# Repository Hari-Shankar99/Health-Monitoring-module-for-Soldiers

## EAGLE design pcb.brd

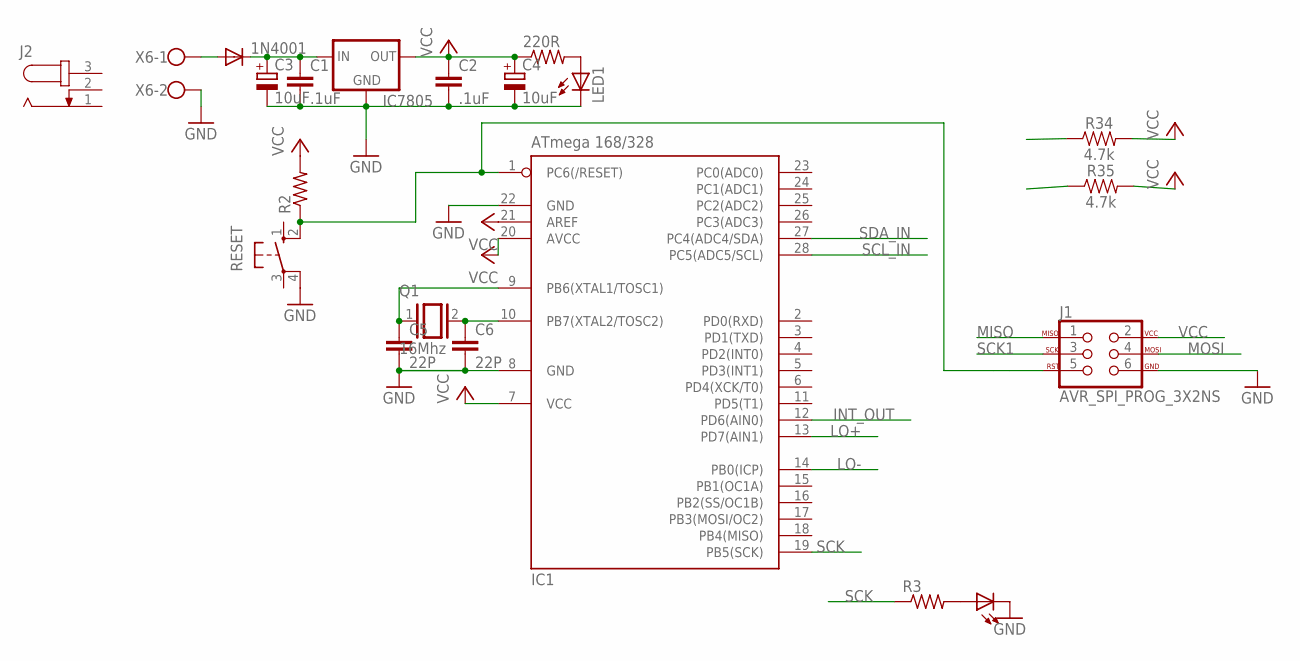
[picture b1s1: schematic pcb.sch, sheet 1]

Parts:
1N4001: BYT85; DO220S
220R: R-US_0204/7; 0204/7
C1, C2: .1uF; C025-024X044
C3, C4: 10uF; E1,8-4
C5, C6: 22P; C025-024X044
IC1: ATmega 168/328; DIL28-3
IC7805: 78XXS
J1: AVR_SPI_PROG_3X2NS; 2X3-NS
J2: JACK-PLUG0; SPC4077
LED1, LED2: LED3MM
Q1: 16Mhz; QS
R2, R3: R-US_0204/7; 0204/7
R34, R35: 4.7k; 0603
RESET: 10-XX; B3F-10XX
X6: W237-102

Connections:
GND: C1.2, C2.2, C3.-, C4.-, C5.2, C6.2, IC1.8 (GND), IC1.22 (GND), IC7805.GND, J1.6, LED1.K (C), LED2.K (C), RESET.4 (P1), X6.2; also elsewhere on the board
INT_OUT: IC1.12 (PD6(AIN0)); also elsewhere on the board
LO+: IC1.13 (PD7(AIN1)); also elsewhere on the board
LO-: IC1.14 (PB0(ICP)); also elsewhere on the board
MISO: J1.1
MOSI: J1.4
unnamed: 1N4001.C, C1.1, C3.+, IC7805.IN
unnamed: 1N4001.A, X6.1
unnamed: 220R.2, LED1.A
unnamed: C6.1, IC1.10 (PB7(XTAL2/TOSC2)), Q1.2
unnamed: C5.1, IC1.9 (PB6(XTAL1/TOSC1)), Q1.1
unnamed: IC1.1 (PC6(/RESET)), J1.5, R2.1, RESET.2 (S1)
unnamed: LED2.A, R3.2
SCK: IC1.19 (PB5(SCK)), R3.1
SCK1: J1.3
SCL_IN: IC1.28 (PC5(ADC5/SCL)); also elsewhere on the board
SDA_IN: IC1.27 (PC4(ADC4/SDA)); also elsewhere on the board
VCC: 220R.1, C2.1, C4.+, IC1.7 (VCC), IC1.20 (AVCC), IC1.21 (AREF), IC7805.OUT, J1.2, R2.2, R34.2, R35.2; also elsewhere on the board

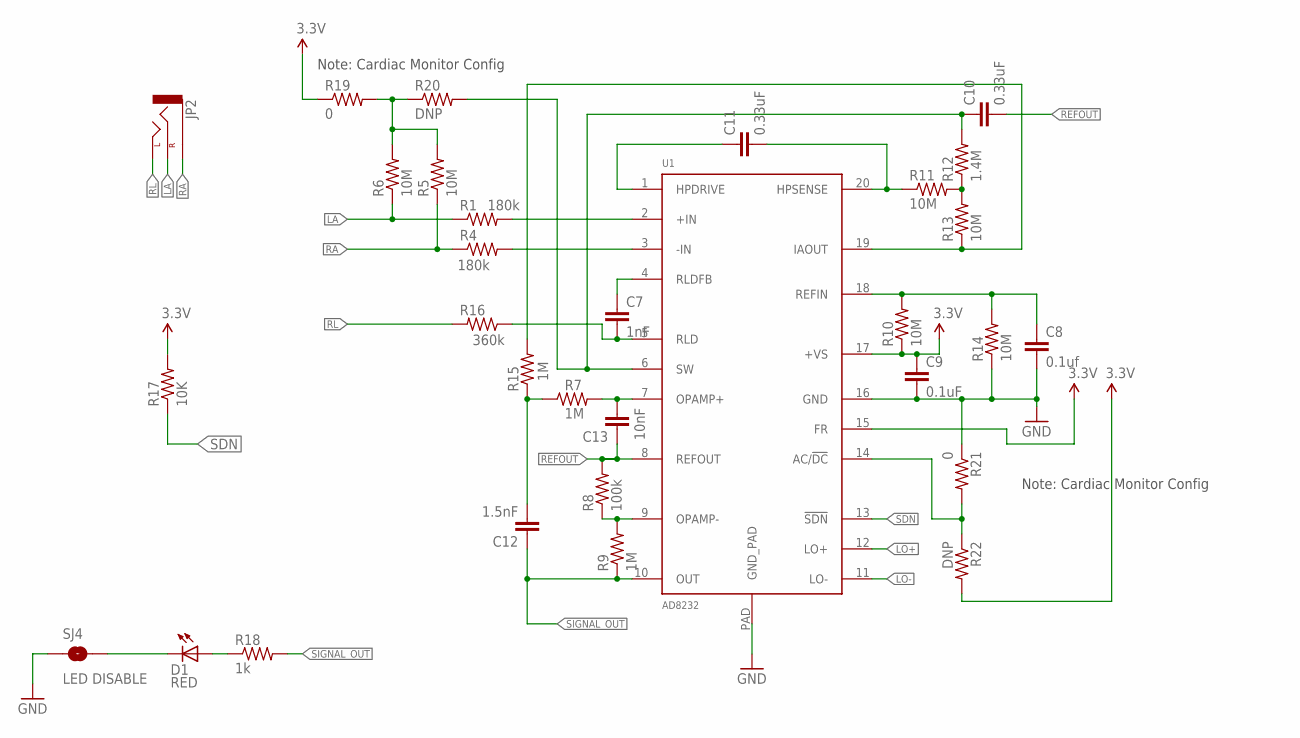
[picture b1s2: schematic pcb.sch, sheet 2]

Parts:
C7: 1nF; 0603-CAP
C8: 0.1uf; 0603-CAP
C9: 0.1uF; 0603-CAP
C10, C11: 0.33uF; 0805
C12: 1.5nF; 0603-CAP
C13: 10nF; 0603-CAP
D1: RED; LED-0603
JP2: AUDIO-JACKSMD2; AUDIO-JACK-3.5MM-SMD
R1, R4: 180k; 0603-RES
R5, R6, R10, R11, R13, R14: 10M; 0603-RES
R7, R9, R15: 1M; 0603-RES
R8: 100k; 0603-RES
R12: 1.4M; 0603-RES
R16: 360k; 0603-RES
R17: 10K; 0603-RES
R18: 1k; 0603-RES
R19, R21: 0; 0603
R20, R22: DNP; 0603
SJ4: LED DISABLE; SJ_2S-TRACE
U1: AD8232; LFCSP_20

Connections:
3.3V: C9.1, R10.1, R17.2, R19.1, R22.2, U1.15 (FR), U1.17 (+VS)
GND: C8.2, C9.2, R14.1, R21.1, SJ4.1, U1.16 (GND), U1.PAD (GND_PAD); also elsewhere on the board
LA: JP2.RING (RIGHT), R1.1, R6.1
LO+: U1.12 (LO+); also elsewhere on the board
LO-: U1.11 (LO-); also elsewhere on the board
unnamed: R1.2, U1.2 (+IN)
unnamed: R4.2, U1.3 (-IN)
unnamed: C13.2, R7.2, U1.7 (OPAMP+)
unnamed: C11.2, R11.1, U1.20 (HPSENSE)
unnamed: C8.1, R10.2, R14.2, U1.18 (REFIN)
unnamed: R8.1, R9.2, U1.9 (OPAMP-)
unnamed: C11.1, U1.1 (HPDRIVE)
unnamed: R11.2, R12.1, R13.2
unnamed: C10.1, R12.2, R20.2, U1.6 (SW)
unnamed: C7.1, U1.4 (RLDFB)
unnamed: C12.2, R7.1, R15.1
unnamed: C7.2, R16.1, U1.5 (RLD)
unnamed: R13.1, R15.2, U1.19 (IAOUT)
unnamed: R5.2, R6.2, R19.2, R20.1
unnamed: D1.A, R18.1
unnamed: D1.C, SJ4.2
unnamed: R21.2, R22.1, U1.14 (AC/!DC)
RA: JP2.SLEEVE, R4.1, R5.1
REFOUT: C10.2, C13.1, R8.2, U1.8 (REFOUT)
RL: JP2.TIP (LEFT), R16.2
SDN: R17.1, U1.13 (!SDN)
SIGNAL_OUT: C12.1, R9.1, R18.2, U1.10 (OUT)

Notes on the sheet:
Note: Cardiac Monitor Config

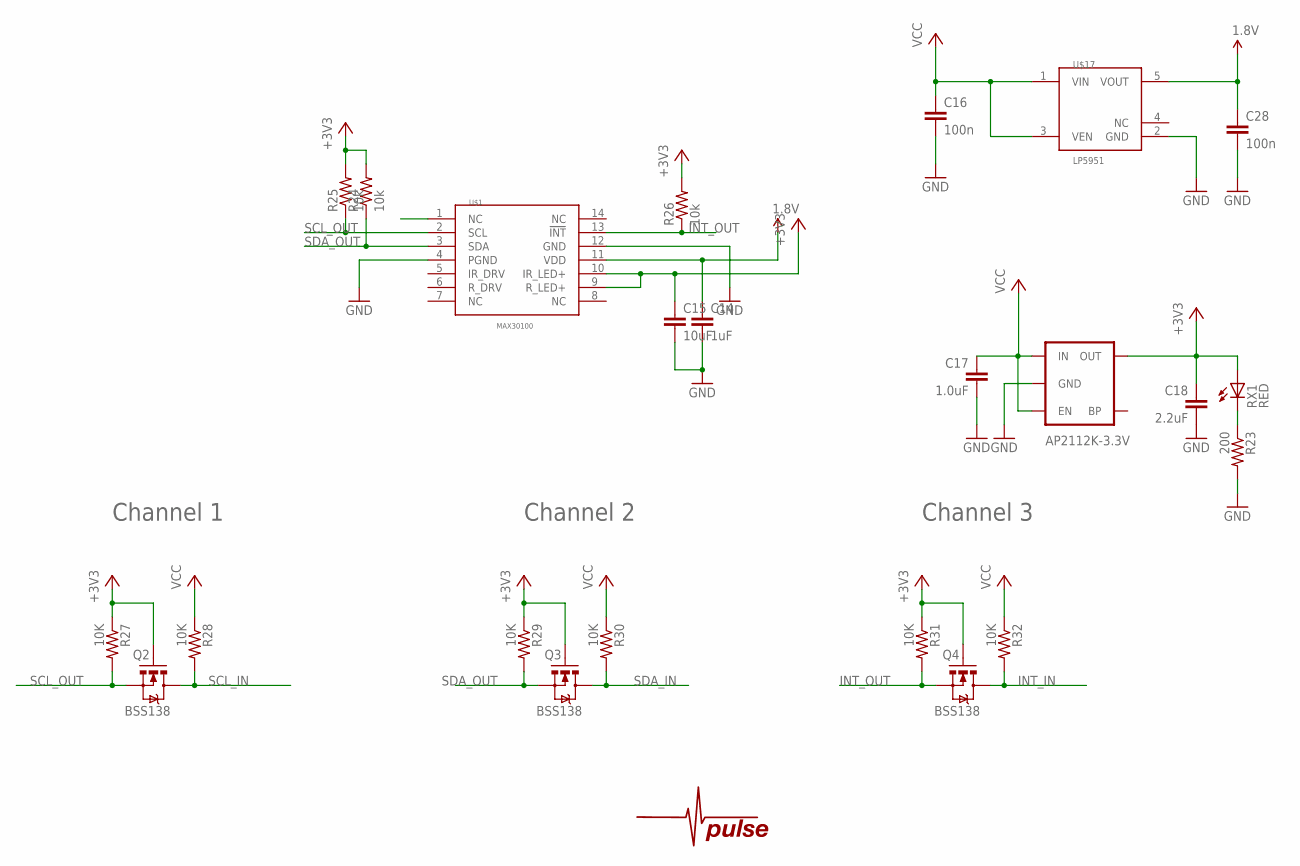
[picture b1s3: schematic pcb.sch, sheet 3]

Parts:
C14: 1uF; C0805
C15: 10uF; C0805
C16, C28: 100n; C0402
C17: 1.0uF; 0805
C18: 2.2uF; C0805
Q2, Q3, Q4: BSS138; SOT23-3
R23: 200; R0402
R24, R25, R26: 10k; R0402
R27, R28, R29, R30, R31, R32: 10K; 0402-RES
RX1: RED; CHIPLED_0603
U2: AP2112K-3.3V; SOT23-5
U$1: MAX30100; OESIP-14
U$3: PROTY_LOGO_WITH_TEXT; PROTY_WITH_TEXT
U$4: PULSE
U$17: LP5951; SC70-5

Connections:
1.8V: C14.1, C28.1, U$1.11 (VDD), U$17.5 (VOUT)
+3V3: C15.1, C18.1, Q2.1 (G), Q3.1 (G), Q4.1 (G), R24.2, R25.2, R26.2, R27.1, R29.1, R31.1, RX1.A, U2.5 (OUT), U$1.9 (R_LED+), U$1.10 (IR_LED+)
GND: C14.2, C15.2, C16.2, C17.2, C18.2, C28.2, R23.2, U2.2 (GND), U$1.4 (PGND), U$1.12 (GND), U$17.2 (GND); also elsewhere on the board
INT_IN: Q4.3 (D), R32.2
INT_OUT: Q4.2 (S), R26.1, R31.2, U$1.13 (!INT); also elsewhere on the board
unnamed: R23.1, RX1.C
unnamed: C17.1, U2.1 (IN), U2.3 (EN)
SCL_IN: Q2.3 (D), R28.2; also elsewhere on the board
SCL_OUT: Q2.2 (S), R25.1, R27.2, U$1.2 (SCL)
SDA_IN: Q3.3 (D), R30.2; also elsewhere on the board
SDA_OUT: Q3.2 (S), R24.1, R29.2, U$1.3 (SDA)
VCC: C16.1, R28.1, R30.1, R32.1, U$17.1 (VIN), U$17.3 (VEN); also elsewhere on the board

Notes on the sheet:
Channel 1
Channel 2
Channel 3

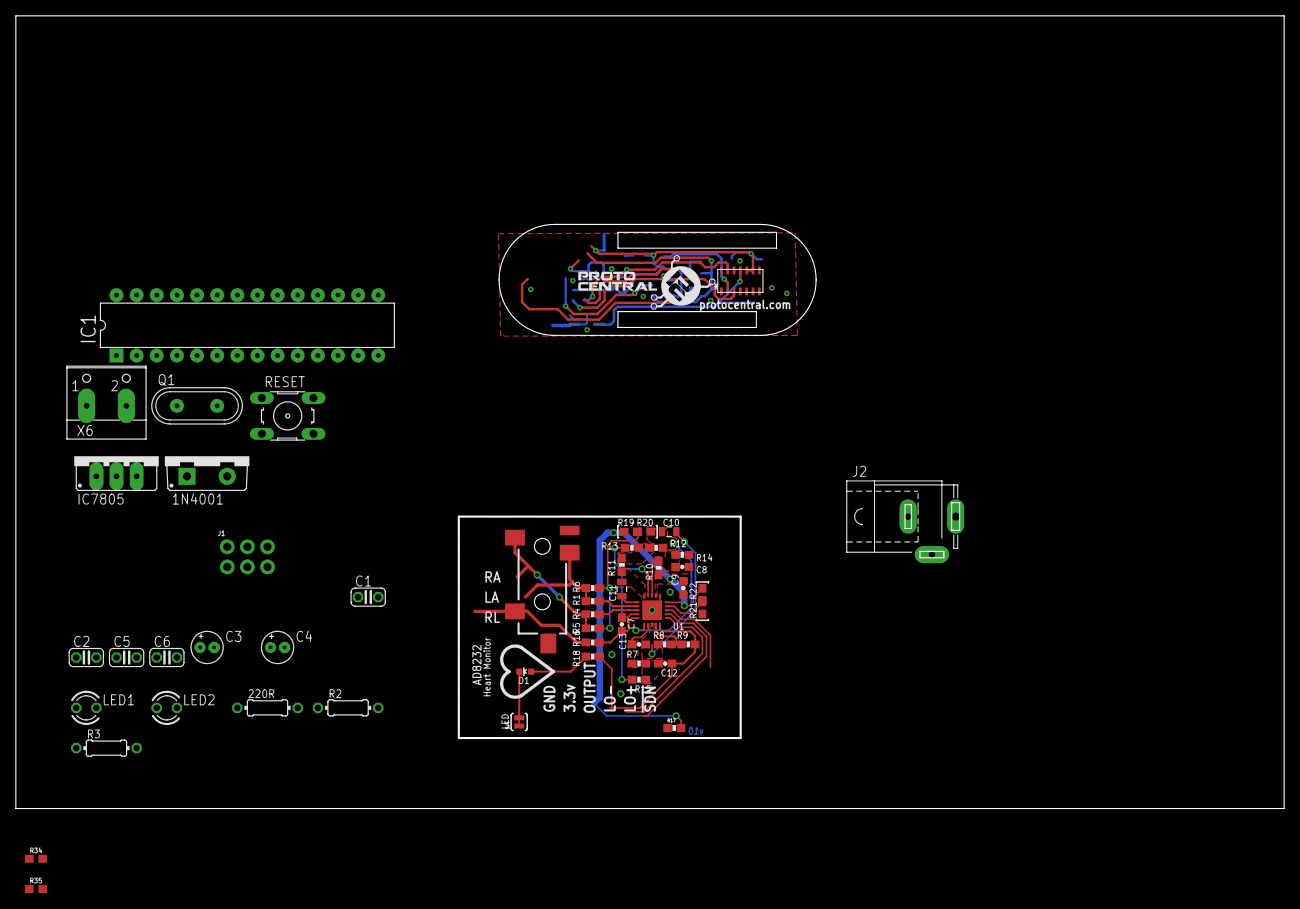
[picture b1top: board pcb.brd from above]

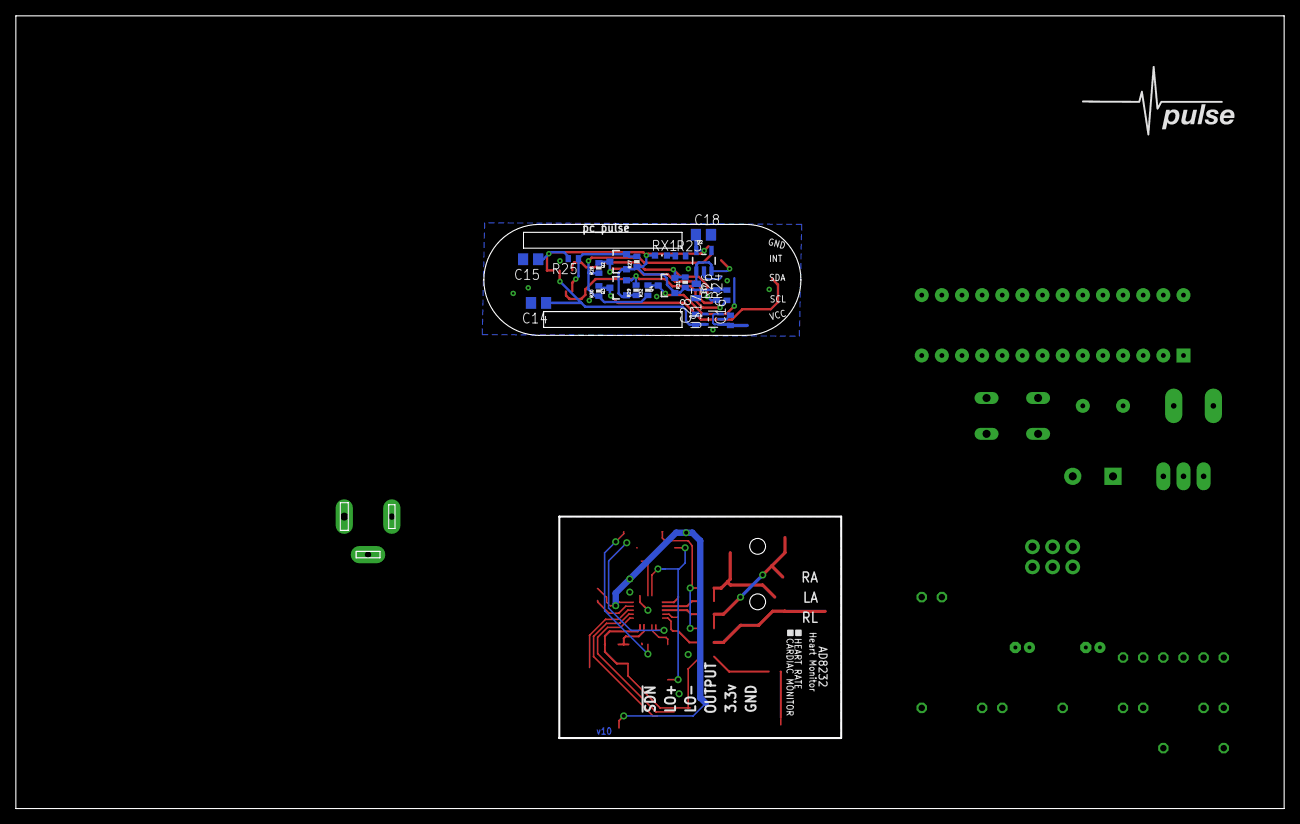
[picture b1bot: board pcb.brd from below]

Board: 2 copper layers, 159.7 x 99.7 mm, 77 parts (23 on the bottom side), 46 nets.

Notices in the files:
parts and their libraries:
SparkFun-Passives: Licensing: CC v3.0 Share-Alike You are welcome to use this library for commercial purposes.
SparkFun-PowerIC: Licensing: Creative Commons ShareAlike 4.0 International - https://creativecommons.org/licenses/by-sa/4.0
